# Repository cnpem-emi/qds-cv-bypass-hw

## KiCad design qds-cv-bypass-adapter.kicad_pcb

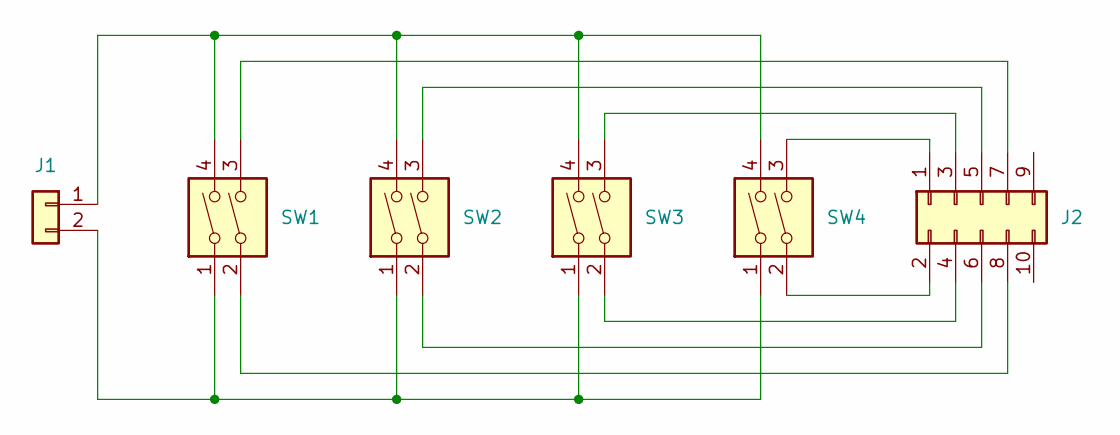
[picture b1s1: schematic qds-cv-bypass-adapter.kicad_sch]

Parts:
J1: Conn_01x02; PhoenixContact_MCV_1,5_2-G-3.81_1x02_P3.81mm_Vertical
J2: Conn_02x05_Odd_Even; SBH11PBPCD05STBK
SW1, SW2, SW3, SW4: SW_DPST; 204211STR

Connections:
unnamed: J2.1, SW4.3
unnamed: J2.2, SW4.2
unnamed: J2.3, SW3.3
unnamed: J2.4, SW3.2
unnamed: J2.5, SW2.3
unnamed: J2.6, SW2.2
unnamed: J2.7, SW1.3
unnamed: J2.8, SW1.2
unnamed: J1.2, SW1.1, SW2.1, SW3.1, SW4.1
unnamed: J1.1, SW1.4, SW2.4, SW3.4, SW4.4

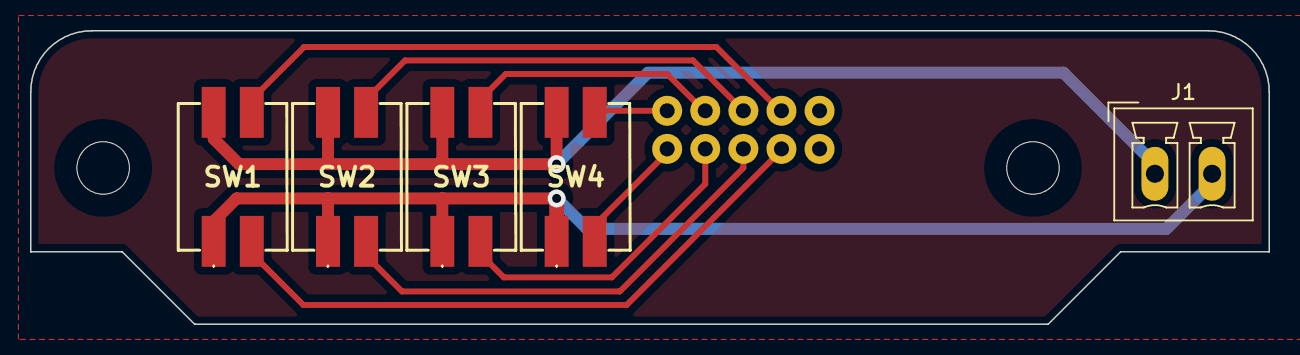
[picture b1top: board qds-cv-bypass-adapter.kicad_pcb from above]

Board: 2 copper layers, 82.6 x 19.6 mm, 6 parts (1 on the bottom side), 10 nets.

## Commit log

2024-03-14 commit inicial
2024-03-19 1a versão fabricada
